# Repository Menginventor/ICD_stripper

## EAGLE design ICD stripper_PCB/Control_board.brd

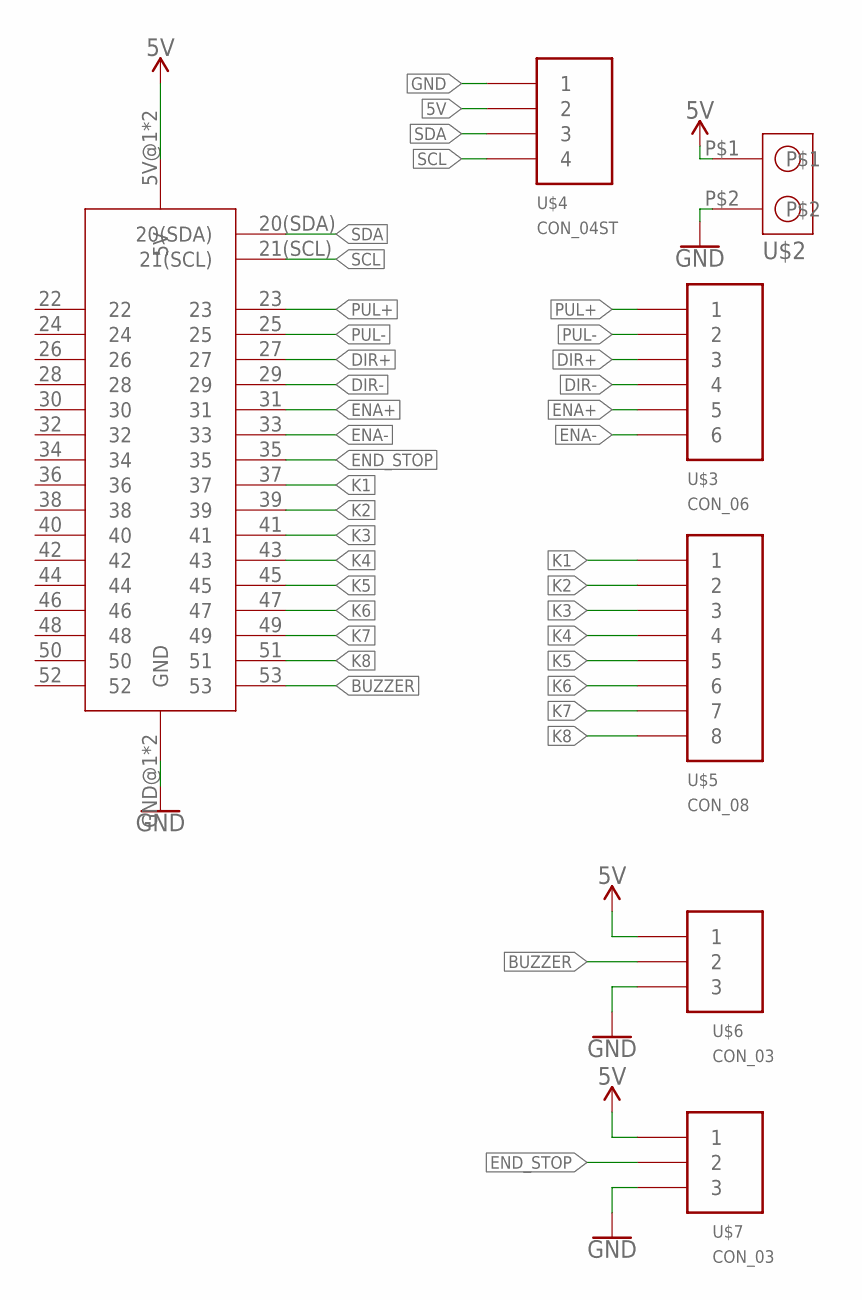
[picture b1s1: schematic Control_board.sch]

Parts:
U$1: ARDUINO_MEGA_SHIELD
U$2: SCREW_TERMINAL-2P
U$3: CON_06; 6-PIN
U$4: CON_04ST; 4-PIN
U$5: CON_08; 8-PIN
U$6, U$7: CON_03; 3-PIN

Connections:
5V: U$1.5V@1 (5V), U$1.5V@2 (5V), U$2.P$1, U$4.3 (2), U$6.3 (1), U$7.3 (1)
BUZZER: U$1.53, U$6.2
DIR+: U$1.27, U$3.3
DIR-: U$1.29, U$3.4
ENA+: U$1.31, U$3.5
ENA-: U$1.33, U$3.6
END_STOP: U$1.35, U$7.2
GND: U$1.GND@1 (GND), U$1.GND@2 (GND), U$2.P$2, U$4.4 (1), U$6.1 (3), U$7.1 (3)
K1: U$1.37, U$5.1
K2: U$1.39, U$5.2
K3: U$1.41, U$5.3
K4: U$1.43, U$5.4
K5: U$1.45, U$5.5
K6: U$1.47, U$5.6
K7: U$1.49, U$5.7
K8: U$1.51, U$5.8
PUL+: U$1.23, U$3.1
PUL-: U$1.25, U$3.2
SCL: U$1.21(SCL), U$4.1 (4)
SDA: U$1.20(SDA), U$4.2 (3)

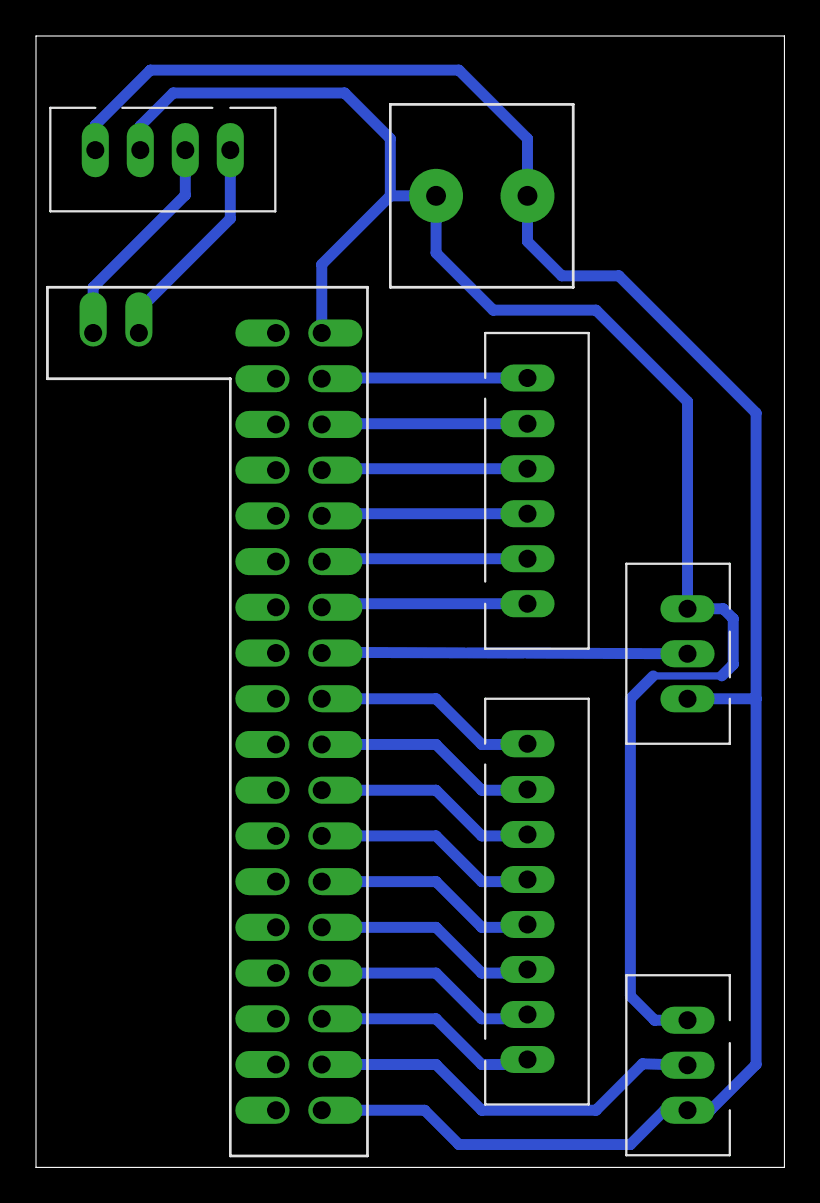
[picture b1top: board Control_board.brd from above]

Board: 2 copper layers, 41.6 x 62.9 mm, 7 parts (0 on the bottom side), 20 nets.

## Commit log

2019-03-17 init
2019-03-17 bug fix
    max 100 RPM UNUSEABLE FIXED
2019-03-23 edit max_rpm

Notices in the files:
parts and their libraries:
SparkFun-PowerSymbols: Licensing: Creative Commons ShareAlike 4.0 International - https://creativecommons.org/licenses/by-sa/4.0
